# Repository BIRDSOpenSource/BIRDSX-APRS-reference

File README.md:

<div align="center">
  
</div> 

<div align="center">
  
</div>

# BIRDSX-APRS-reference
 Documentation for the APRS Reference files of the BIRDSX Satellite.

## About the BIRDSX Program:

The Mission Statement of the Project is:

> “The goal of our project is to bring diversity to the space sector and democratize the usage of space.”

The project is led by Kyushu Institute of Technology in Japan and involves students from XXX,XXX and Japan.

Satellite Names: Dragonfly (Japan), 

Stakeholders:  Our stakeholders are Kyushu Institute of Technology (Kyutech) and the Association for Radio Digital Communications (ARDC).

Project duration: 2023-2024

CubeSat: 2U (20x10x10) cm3

Weight: 1.13kg

Launch Date: 21st February 2025

BIRDS-X project is a 2U CubeSat dedicated to amateur radio communication.

## Organisation structure

```bash

├── .gitattributes
├── BIRDS_Solar-panel-attachment-procedure_v2.2.pdf
├── Manual (SML-2K1MV1) (1).pdf
├── LICENSE
└── README.md

```

## Features

## I like this project, can I help you?
You are welcome 🙂

* Give us a star ⭐
* Watch repository to be notified about updates 👀
* If you will find some errors, report them in Issues 🐞
* Try Birds designs on some real computer and let us know how it worked in Discussions. 💬
* We would greatly appreciate if you would also tell others about this ecosystem, it helps us to improve BIRDS Open Source. Thank you!

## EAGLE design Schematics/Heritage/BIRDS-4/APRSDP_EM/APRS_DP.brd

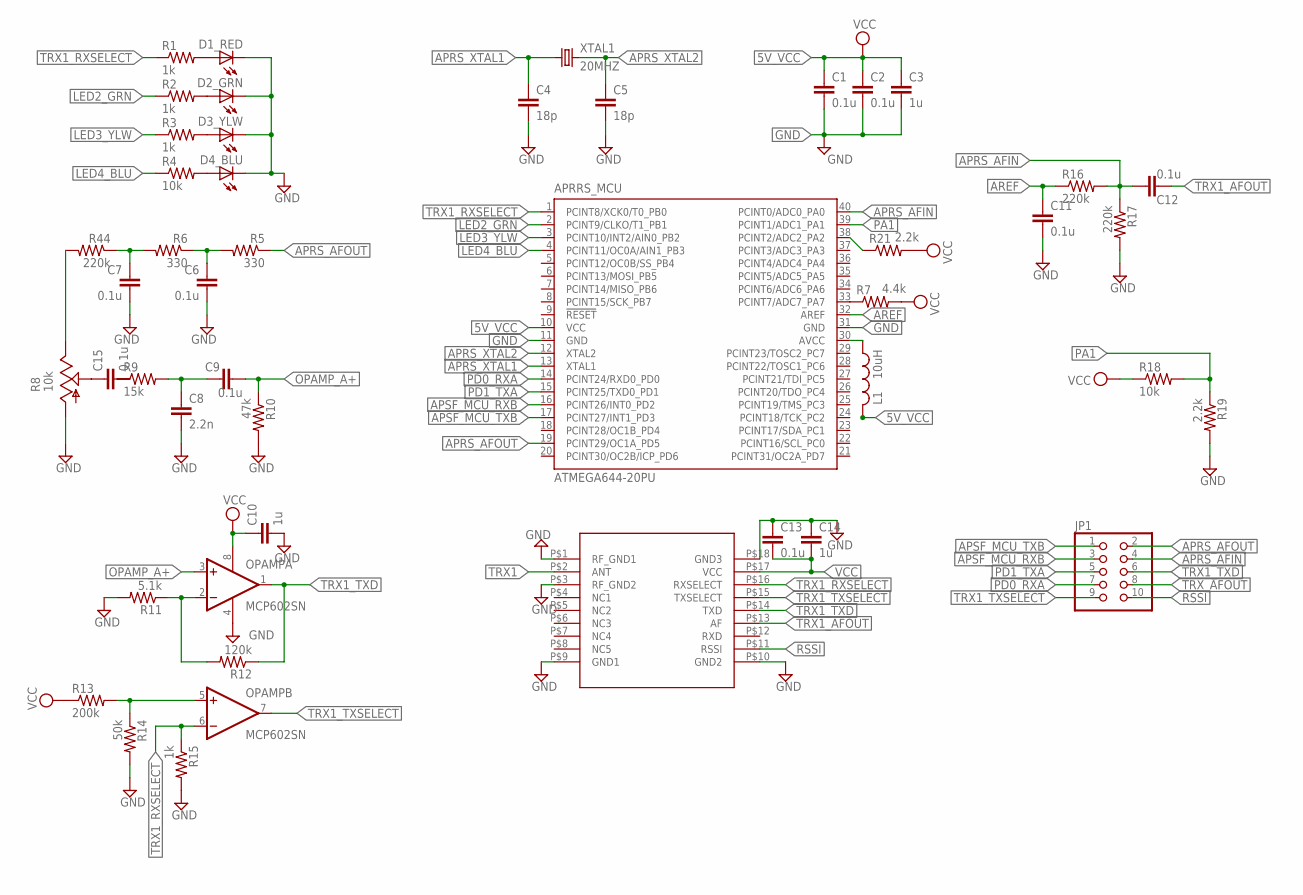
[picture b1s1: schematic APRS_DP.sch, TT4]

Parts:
APRRS_MCU: ATMEGA644-20PU; DIL40
BIM1H(TRX1)1: BIM1H
C1, C2, C6, C7, C9, C11, C12, C13, C15: 0.1u; C0805
C3, C10, C14: 1u; C0805
C4, C5: 18p; C0805
C8: 2.2n; C0805
D1_RED, D2_GRN, D3_YLW, D4_BLU: LEDSML0805; SML0805
JP1: PINHD-2X5; 2X05
L1: 10uH; L2012C
OPAMP: MCP602SN; SO08
R1, R2, R3, R15: 1k; R0805
R4, R18: 10k; R0805
R5, R6: 330; R0805
R7: 4.4k; R0805
R8: 10k; 3223W
R9: 15k; R0805
R10: 47k; R0805
R11: 5.1k; R0805
R12: 120k; R0805
R13: 200k; R0805
R14: 50k; R0805
R16, R17, R44: 220k; R0805
R19, R21: 2.2k; R0805
XTAL1: 20MHZ; SM49

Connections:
5V_VCC: APRRS_MCU.10 (VCC), C1.1, C2.1, C3.1, L1.2
APRS_AFIN: APRRS_MCU.40 (PCINT0/ADC0_PA0), C12.1, JP1.4, R16.2, R17.1
APRS_AFOUT: APRRS_MCU.19 (PCINT29/OC1A_PD5), JP1.2, R5.1
APRS_XTAL1: APRRS_MCU.13 (XTAL1), C4.1, XTAL1.1
APRS_XTAL2: APRRS_MCU.12 (XTAL2), C5.1, XTAL1.2
APSF_MCU_RXB: APRRS_MCU.16 (PCINT26/INT0_PD2), JP1.3
APSF_MCU_TXB: APRRS_MCU.17 (PCINT27/INT1_PD3), JP1.1
AREF: APRRS_MCU.32 (AREF), C11.1, R16.1
GND: APRRS_MCU.11 (GND), APRRS_MCU.31 (GND), BIM1H(TRX1)1.P$1 (RF_GND1), BIM1H(TRX1)1.P$3 (RF_GND2), BIM1H(TRX1)1.P$9 (GND1), BIM1H(TRX1)1.P$10 (GND2), BIM1H(TRX1)1.P$18 (GND3), C1.2, C2.2, C3.2, C4.2, C5.2, C6.2, C7.2, C8.2, C10.2, C11.2, C13.1, C14.1, D1_RED.C, D2_GRN.C, D3_YLW.C, D4_BLU.C, OPAMP.4 (V-), R8.1 (A), R10.2, R11.2, R14.2, R15.2, R17.2, R19.2
LED2_GRN: APRRS_MCU.2 (PCINT9/CLKO/T1_PB1), R2.1
LED3_YLW: APRRS_MCU.3 (PCINT10/INT2/AIN0_PB2), R3.1
LED4_BLU: APRRS_MCU.4 (PCINT11/OC0A/AIN1_PB3), R4.1
unnamed: APRRS_MCU.30 (AVCC), L1.1
unnamed: C6.1, R5.2, R6.1
unnamed: D1_RED.A, R1.2
unnamed: D2_GRN.A, R2.2
unnamed: D3_YLW.A, R3.2
unnamed: D4_BLU.A, R4.2
unnamed: OPAMP.2 (-IN), R11.1, R12.2
unnamed: C15.1, R8.2 (S)
unnamed: APRRS_MCU.33 (PCINT7/ADC7_PA7), R7.1
unnamed: C7.1, R6.2, R44.1
unnamed: C8.1, C9.1, R9.2
unnamed: R8.3 (E), R44.2
OPAMP_A+: C9.2, OPAMP.3 (+IN), R10.1
OPAMP_B+: OPAMP.5 (+IN), R13.2, R14.1
PA1: APRRS_MCU.39 (PCINT1/ADC1_PA1), R18.2, R19.1
PA2: APRRS_MCU.38 (PCINT2/ADC2_PA2), R21.1
PD0_RXA: APRRS_MCU.14 (PCINT24/RXD0_PD0), JP1.7
PD1_TXA: APRRS_MCU.15 (PCINT25/TXD0_PD1), JP1.5
RSSI: BIM1H(TRX1)1.P$11 (RSSI), JP1.10
TRX1: BIM1H(TRX1)1.P$2 (ANT)
TRX1_AFOUT: BIM1H(TRX1)1.P$13 (AF), C12.2
TRX1_RXSELECT: APRRS_MCU.1 (PCINT8/XCK0/T0_PB0), BIM1H(TRX1)1.P$16 (RXSELECT), OPAMP.6 (-IN), R1.1, R15.1
TRX1_TXD: BIM1H(TRX1)1.P$14 (TXD), JP1.6, OPAMP.1 (OUT), R12.1
TRX1_TXSELECT: BIM1H(TRX1)1.P$15 (TXSELECT), JP1.9, OPAMP.7 (OUT)
TRX_AFOUT: JP1.8
VCC: BIM1H(TRX1)1.P$17 (VCC), C10.1, C13.2, C14.2, OPAMP.8 (V+), R7.2, R13.1, R18.1, R21.2

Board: 4 copper layers, 46 parts (0 on the bottom side), 36 nets, no tracks yet.

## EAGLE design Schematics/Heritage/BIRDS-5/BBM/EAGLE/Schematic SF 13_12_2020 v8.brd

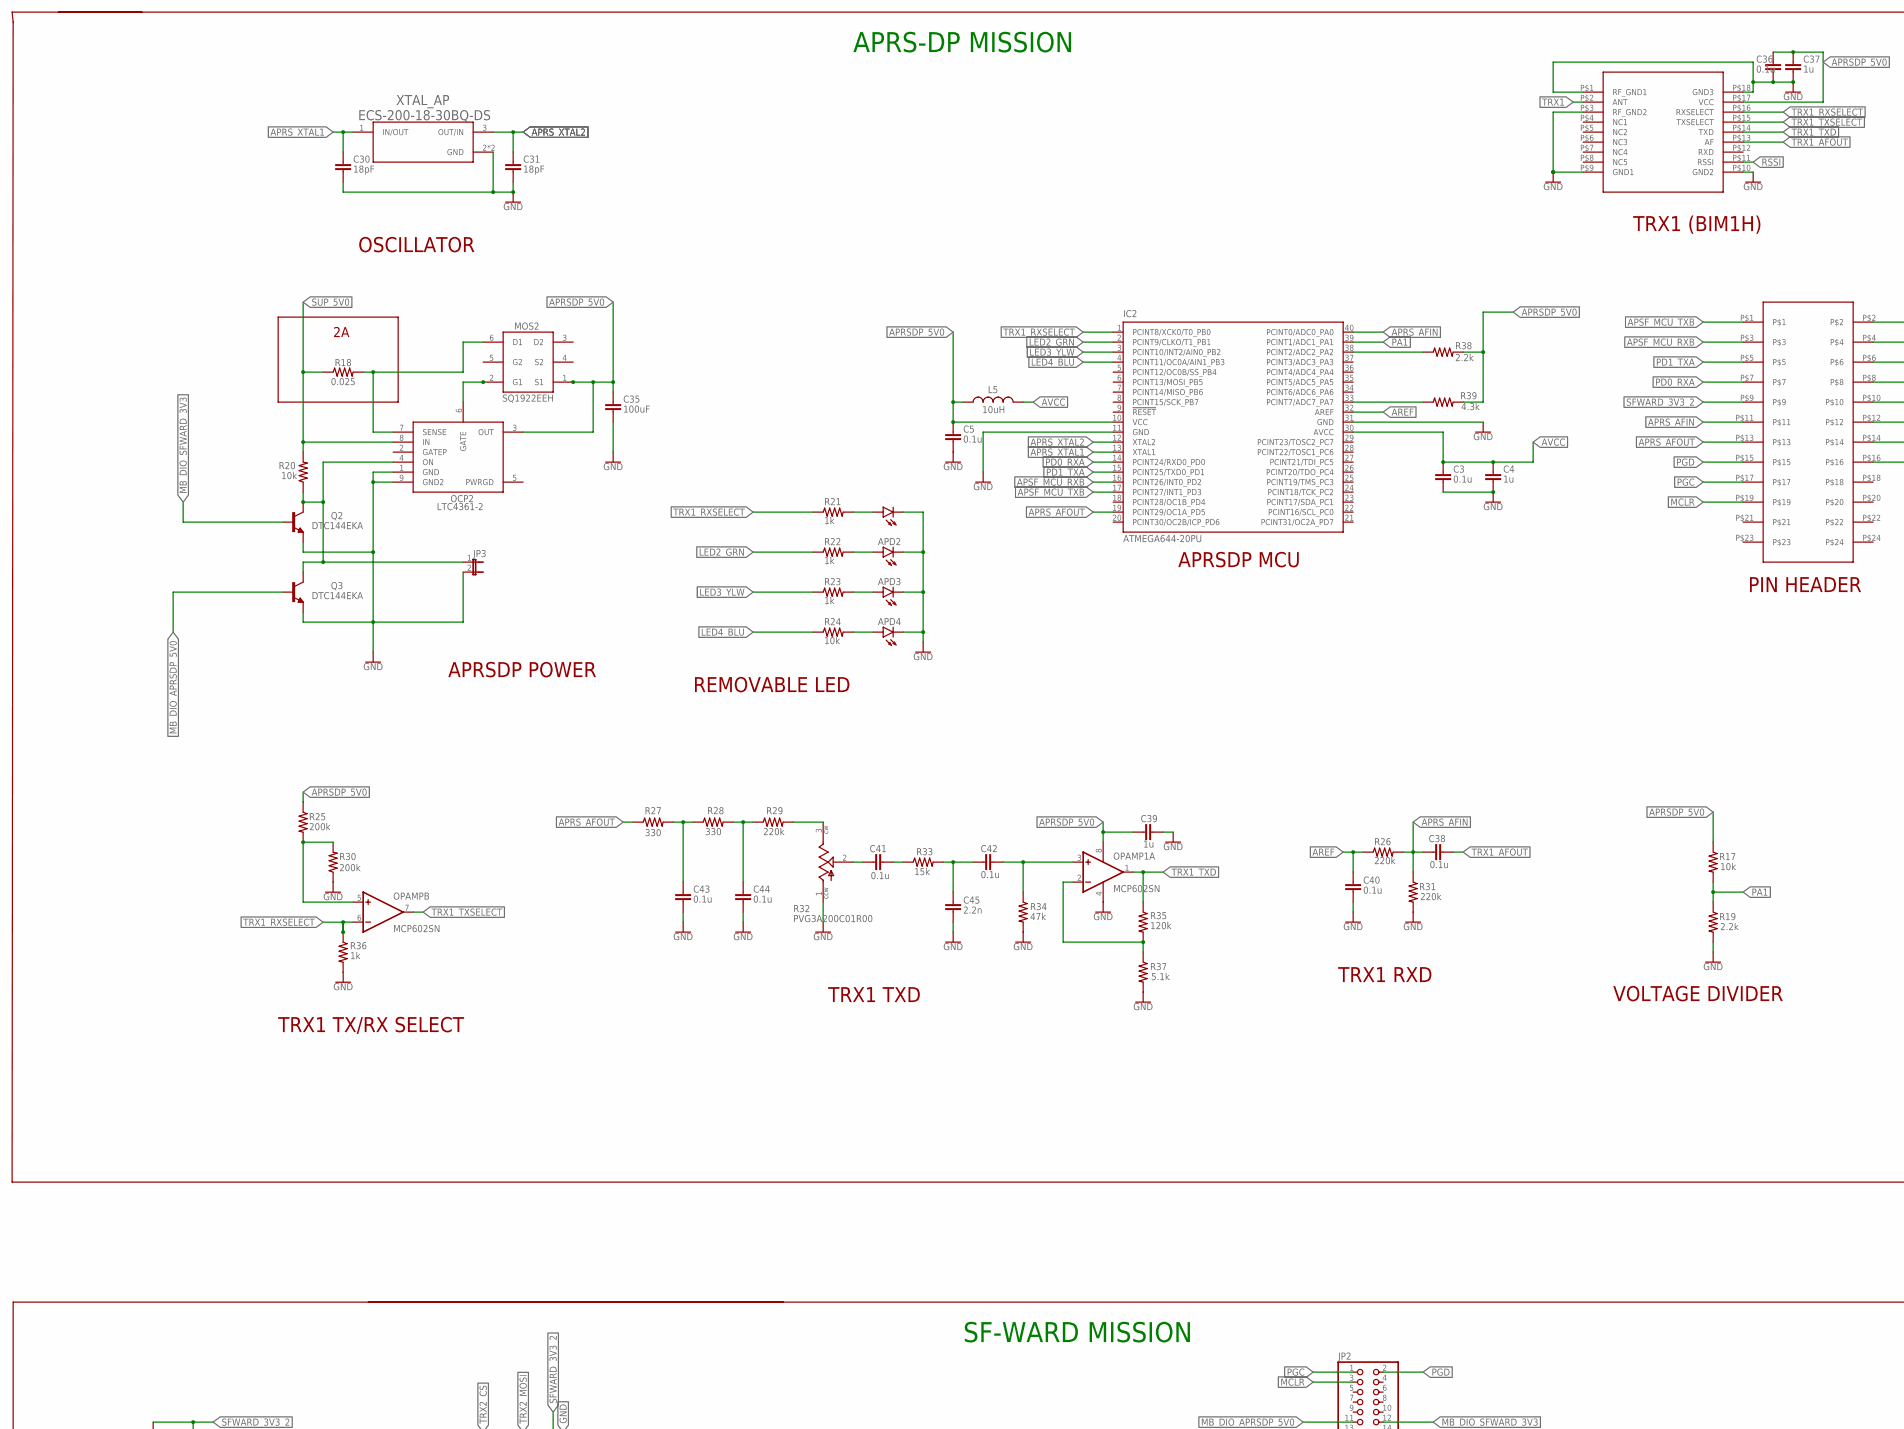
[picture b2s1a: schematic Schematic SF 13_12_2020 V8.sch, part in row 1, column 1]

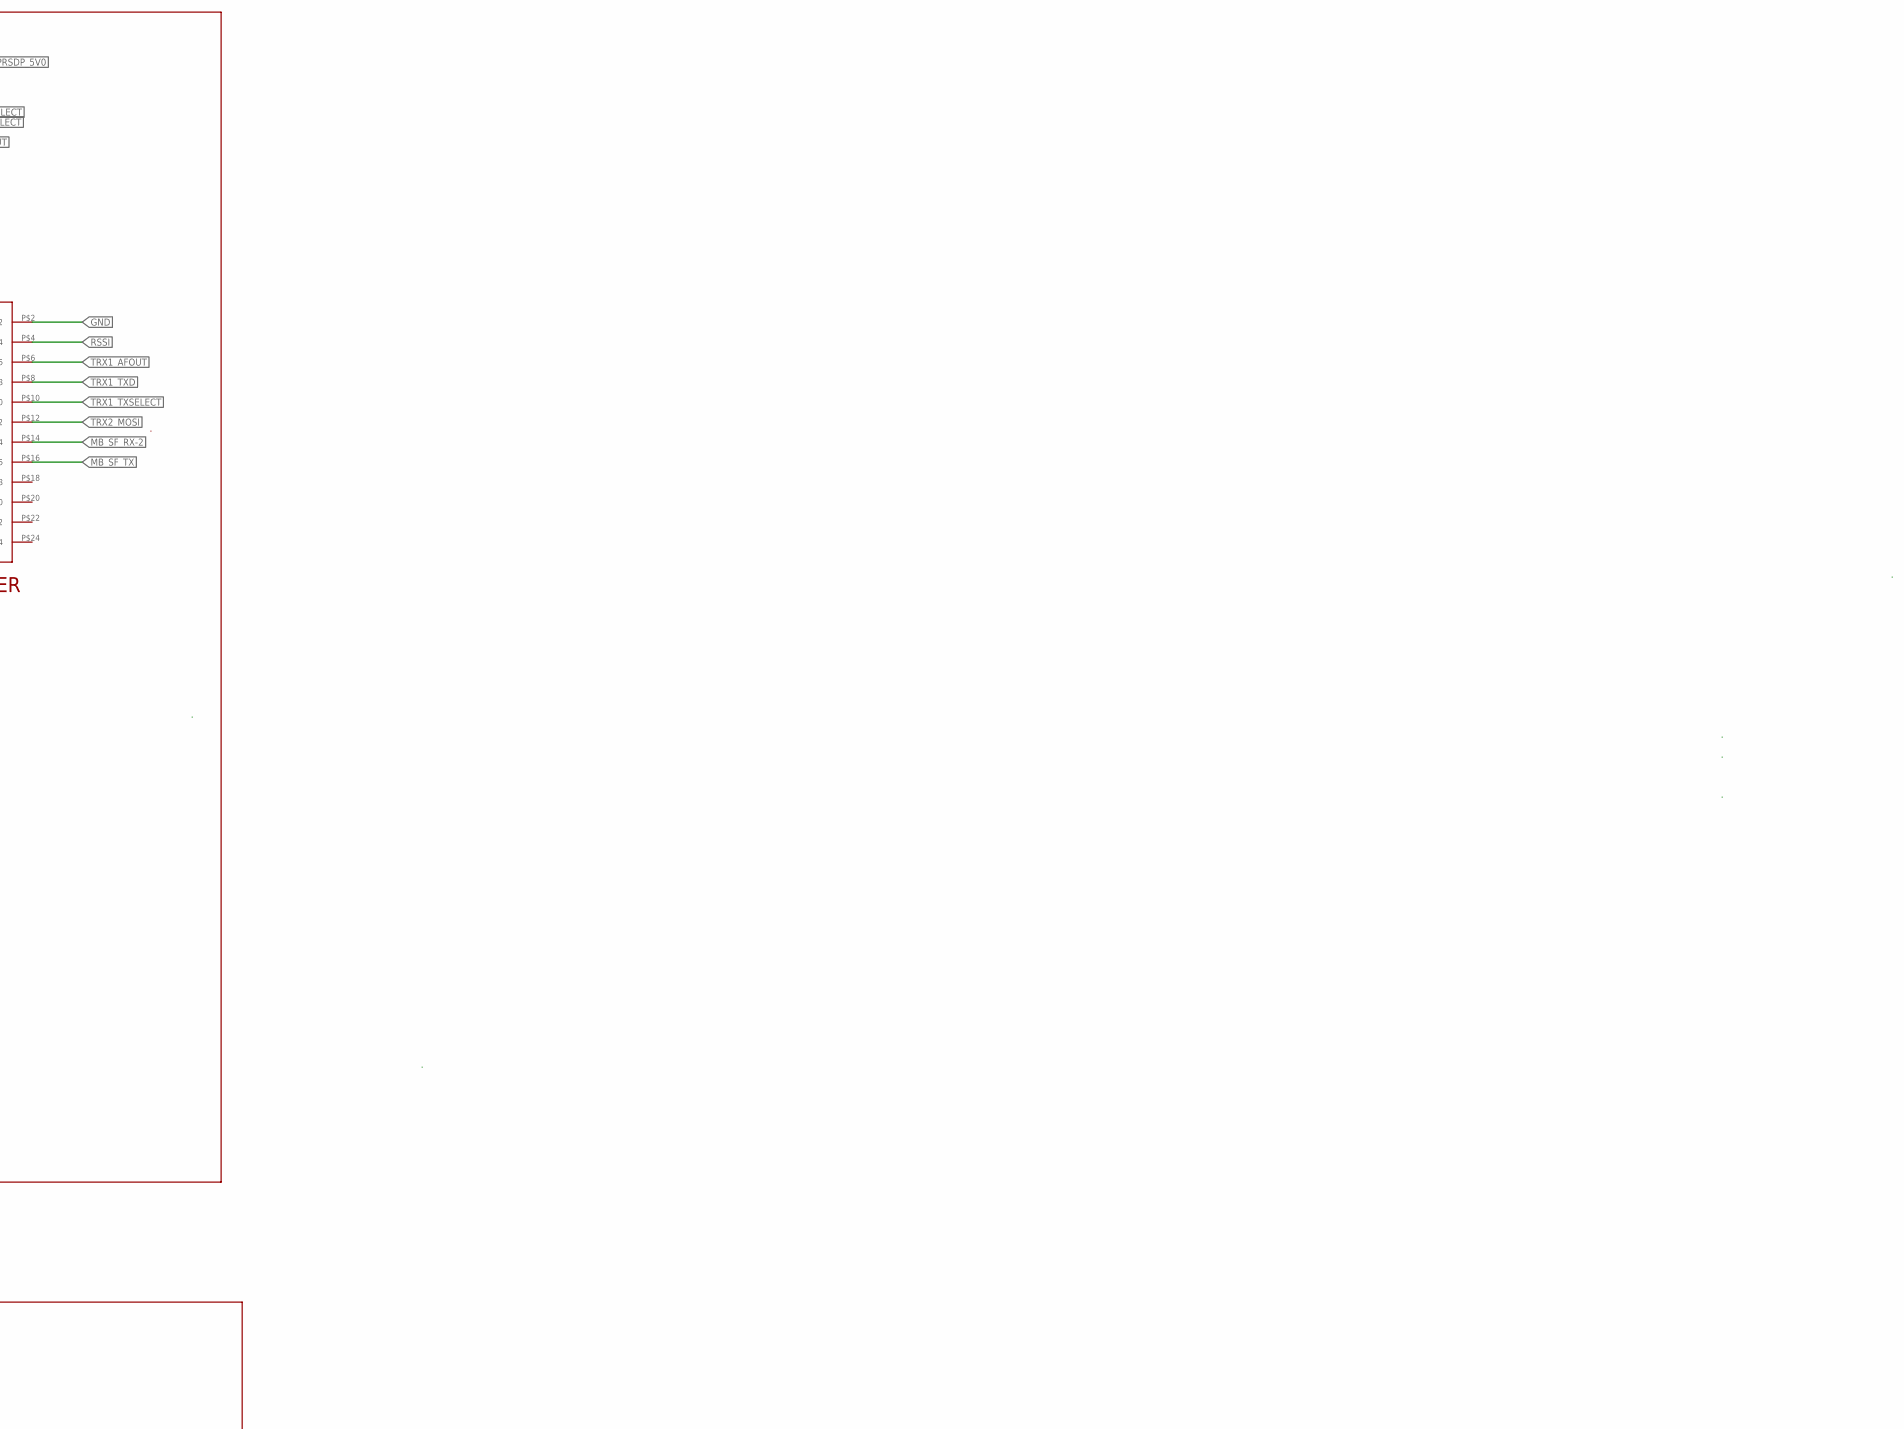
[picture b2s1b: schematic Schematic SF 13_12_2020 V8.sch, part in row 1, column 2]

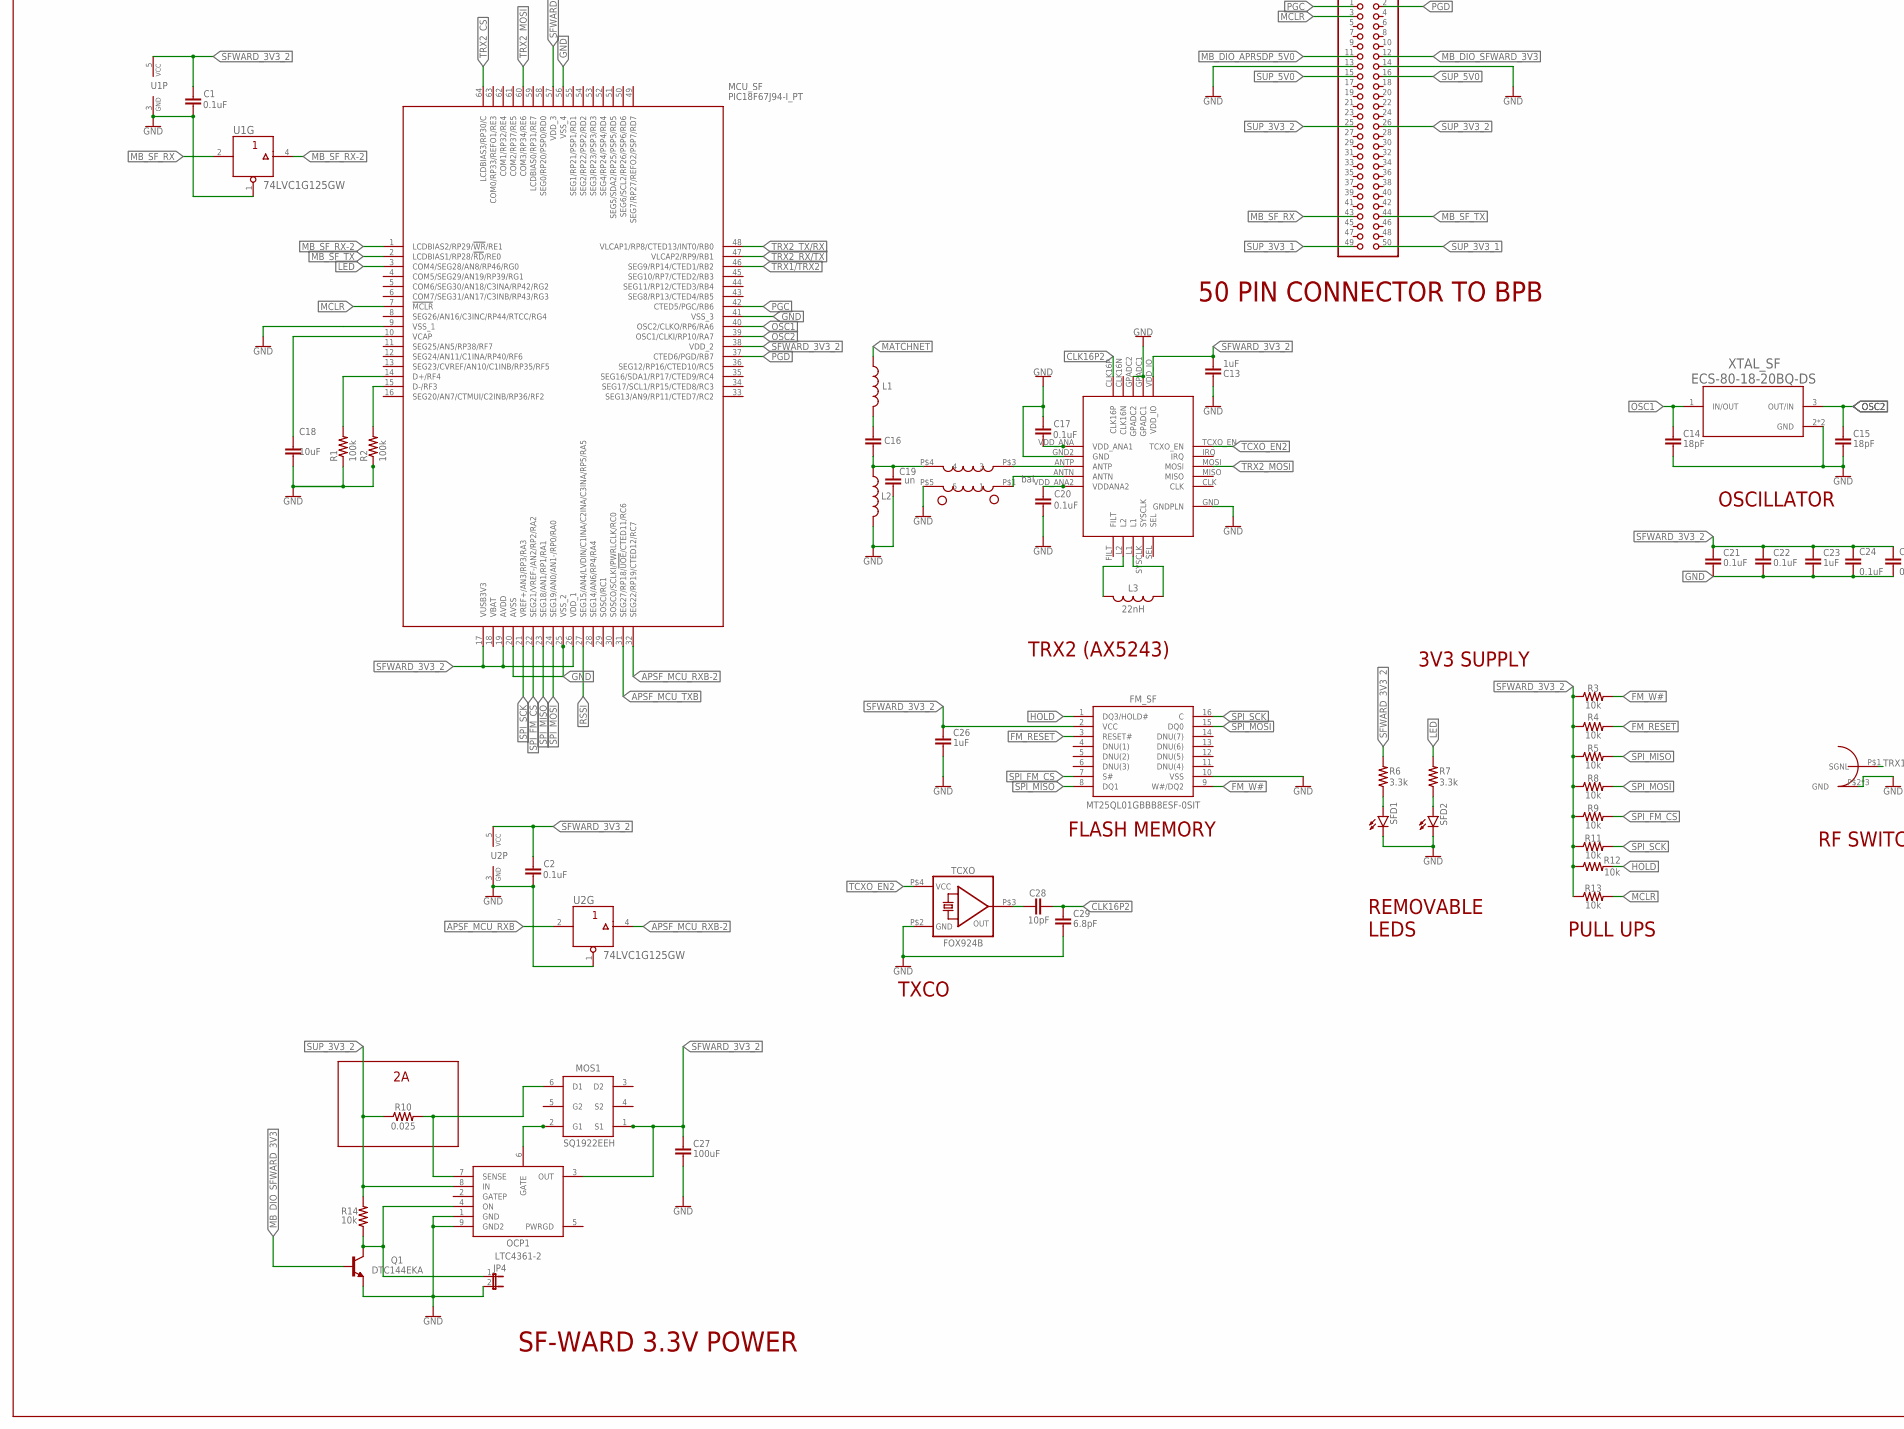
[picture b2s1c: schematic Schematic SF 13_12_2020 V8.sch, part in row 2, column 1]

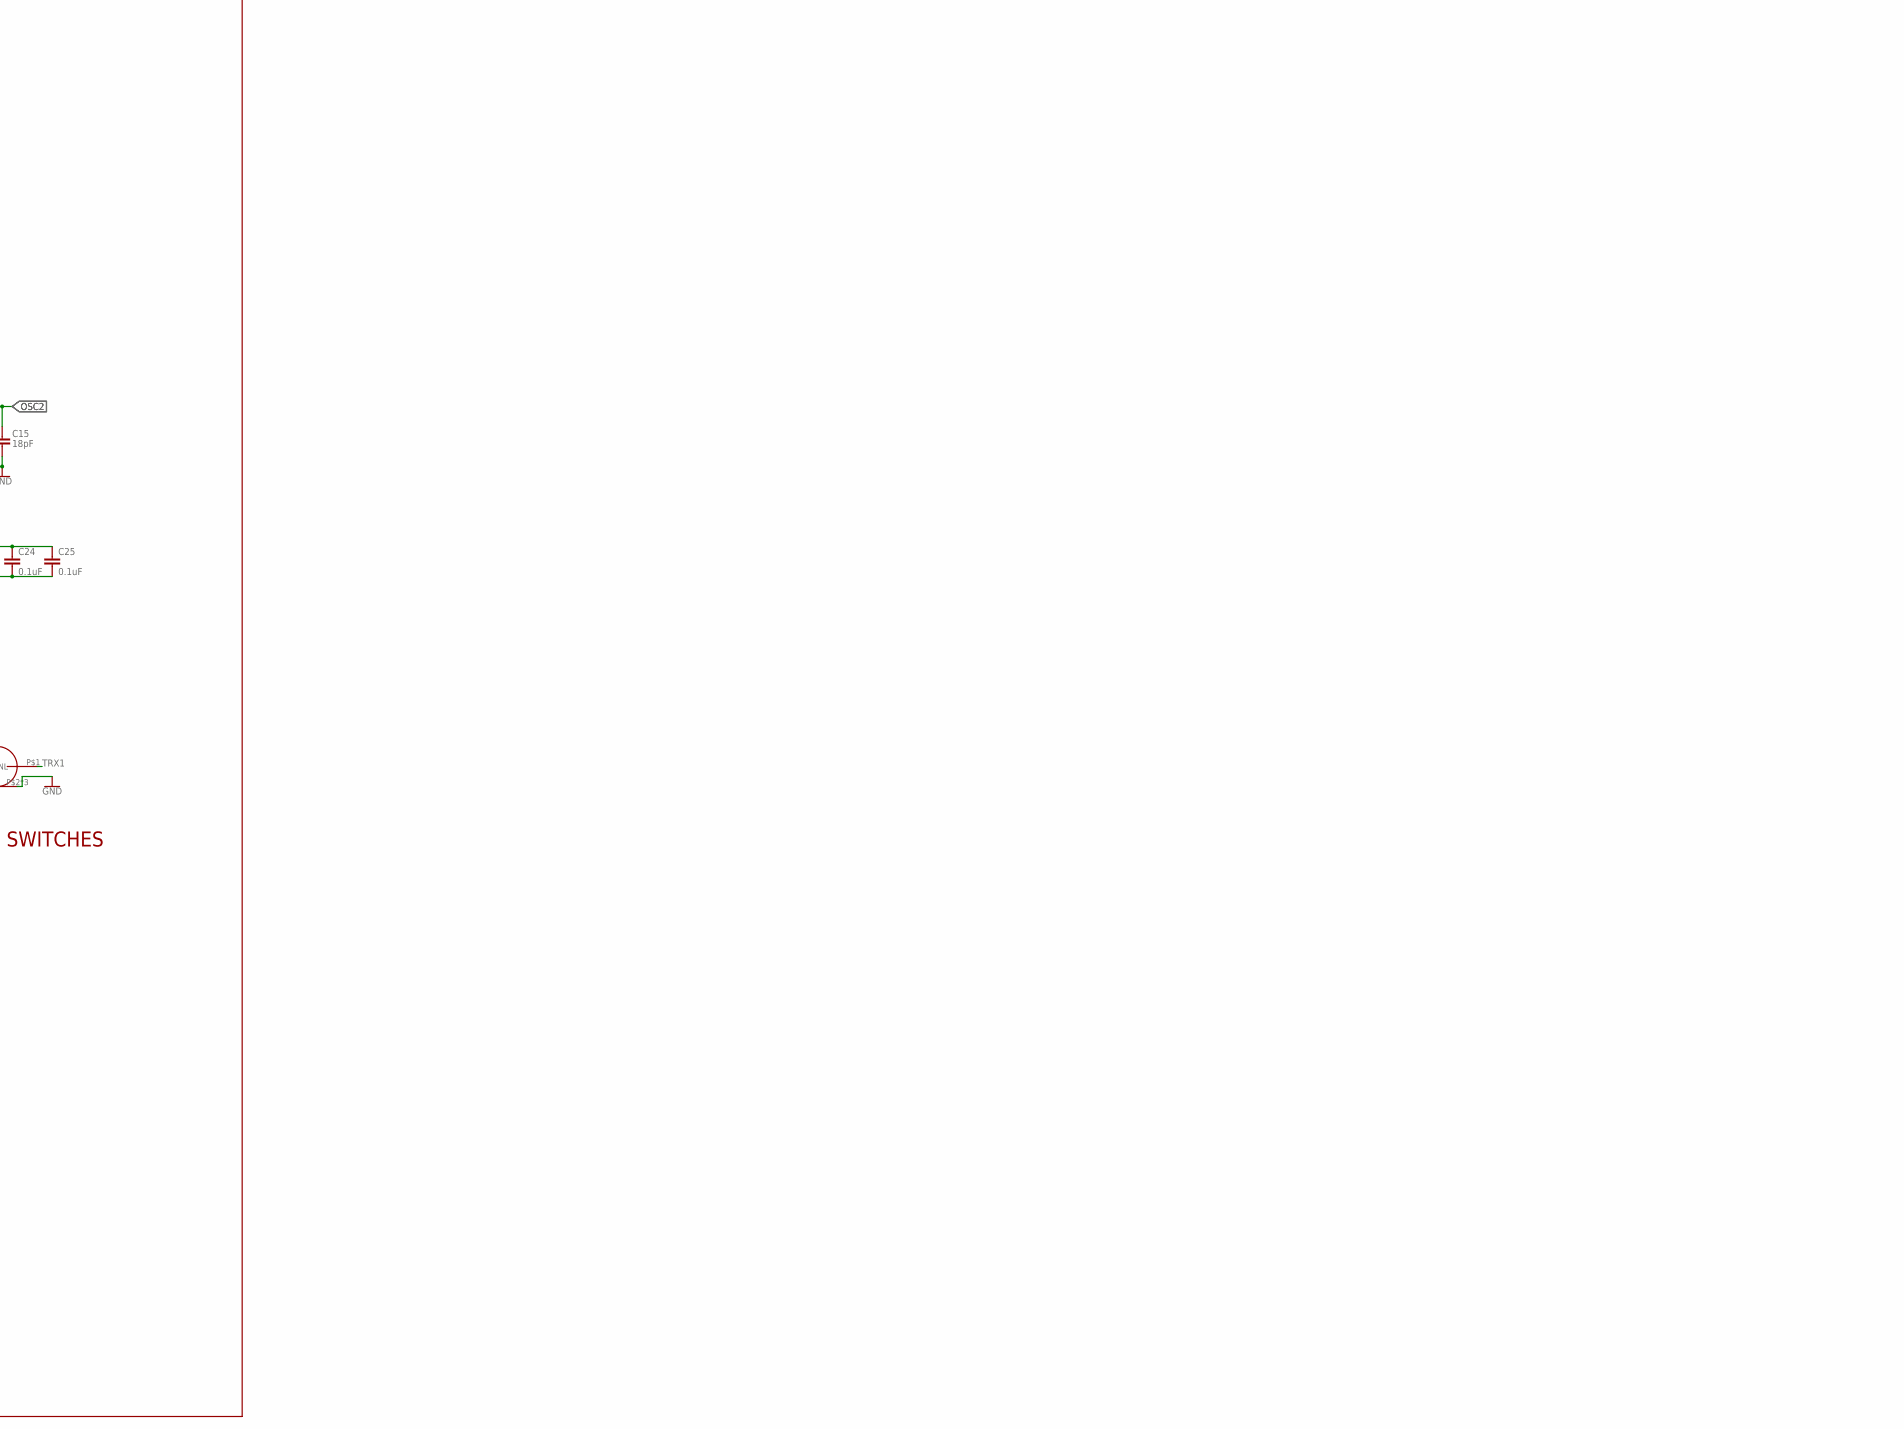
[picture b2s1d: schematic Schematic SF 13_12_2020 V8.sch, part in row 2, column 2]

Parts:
APD1, APD2, APD3, APD4: LEDSML0603; SML0603
BAL: MABA-010245-BALUN
C1, C2, C17, C20, C21, C22, C24, C25: 0.1uF; C0603
C3, C5, C36, C38, C40, C41, C42, C43, C44: 0.1u; C0603
C4, C37, C39: 1u; C0603
C13, C23, C26: 1uF; C0603
C14, C15, C30, C31: 18pF; C0603
C16, C19: C-EUC0805; C0805
C18: 10uF; C0603
C27, C35: 100uF; C0805
C28: 10pF; C0603
C29: 6.8pF; C0603
C45: 2.2n; C0603
FM_SF: MT25QL01GBBB8ESF-0SIT; SOIC127P1032X265-16N
IC2: ATMEGA644-20PU; DIL40
JP1: RAB_ACCESS
JP2: PINHD-2X25_2.00; 2X25M
JP3, JP4: JP1E; JP1
L1, L2: L-USL2012C; L2012C
L3: 22nH; L2012C
L5: 10uH; L2012C
MCU_SF: PIC18F67J94-I_PT; QFP50P1200X1200X120-64N
MOS1, MOS2: SQ1922EEH; SOT65P210X110-6N
OCP1, OCP2: LTC4361-2; DFN
OPAMP, OPAMP1: MCP602SN; SO08
Q1, Q2, Q3: DTC144EKA; SOT346-R
R1, R2: 100k; R0603
R3, R4, R5, R8, R9, R11, R12, R13, R14, R17, R20, R24: 10k; R0603
R6, R7: 3.3k; R0603
R10, R18: 0.025; R0805
R19, R38: 2.2k; R0603
R21, R22, R23, R36: 1k; R0603
R25, R30: 200k; R0603
R26, R29, R31: 220k; R0603
R27, R28: 330; R0603
R32: PVG3A200C01R00; TRIM_PVG3A200C01R00
R33: 15k; R0603
R34: 47k; R0603
R35: 120k; R0603
R37: 5.1k; R0603
R39: 4.3k; R0603
RFCON: MMCX_908_222101T
SFD1, SFD2: LEDCHIPLED_0603; CHIPLED_0603
TCXO: FOX924B
TRX1: BIM1H
TRX2: AX5243
U1, U2: 74LVC1G125GW; SOT353-1
XTAL_AP: ECS-200-18-30BQ-DS; XTAL_ECS-200-18-30BQ-DS
XTAL_SF: ECS-80-18-20BQ-DS; XTAL_ECS-80-18-20BQ-DS

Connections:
APRSDP_5V0: C5.2, C35.1, C36.1, C37.1, C39.1, IC2.10 (VCC), L5.1, MOS2.1 (S1), OCP2.3 (OUT), OPAMP1.8 (V+), R17.1, R25.1, R38.2, R39.2, TRX1.P$17 (VCC)
APRS_AFIN: C38.1, IC2.40 (PCINT0/ADC0_PA0), JP1.P$11, R26.2, R31.1
APRS_AFOUT: IC2.19 (PCINT29/OC1A_PD5), JP1.P$13, R27.1
APRS_XTAL1: C30.1, IC2.13 (XTAL1), XTAL_AP.1 (IN/OUT)
APRS_XTAL2: C31.1, IC2.12 (XTAL2), XTAL_AP.3 (OUT/IN)
APSF_MCU_RXB: IC2.16 (PCINT26/INT0_PD2), JP1.P$3, U2.2 (A)
APSF_MCU_RXB-2: MCU_SF.32 (SEG22/RP19/CTED12/RC7), U2.4 (Y)
APSF_MCU_TXB: IC2.17 (PCINT27/INT1_PD3), JP1.P$1, MCU_SF.31 (SEG27/RP18/!UOE!/CTED11/RC6)
AREF: C40.1, IC2.32 (AREF), R26.1
AVCC: C3.1, C4.1, IC2.30 (AVCC), L5.2
CLK16P2: C28.2, C29.1, TRX2.CLK16P
FM_RESET: FM_SF.3 (RESET#), R4.2
FM_W#: FM_SF.9 (W#/DQ2), R3.2
GATE3: MOS1.2 (G1), OCP1.6 (GATE)
GATE4: MOS2.2 (G1), OCP2.6 (GATE)
GND: APD1.C, APD2.C, APD3.C, APD4.C, BAL.P$5 (5), C1.1, C2.1, C3.2, C4.2, C5.1, C13.1, C14.2, C15.2, C17.2, C18.2, C19.2, C20.2, C21.2, C22.2, C23.2, C24.2, C25.2, C26.2, C27.2, C29.2, C30.2, C31.2, C35.2, C36.2, C37.2, C39.2, C40.2, C43.2, C44.2, C45.2, FM_SF.10 (VSS), IC2.11 (GND), IC2.31 (GND), JP1.P$2, JP2.13, JP2.14, JP3.2, JP4.2, L2.2, MCU_SF.9 (VSS_1), MCU_SF.20 (AVSS), MCU_SF.25 (VSS_2), MCU_SF.41 (VSS_3), MCU_SF.56 (VSS_4), OCP1.1 (GND), OCP1.9 (GND2), OCP2.1 (GND), OCP2.9 (GND2), OPAMP1.4 (V-), Q1.1 (E), Q2.1 (E), Q3.1 (E), R1.1, R2.1, R19.2, R30.1, R31.2, R32.1 (CCW), R34.2, R36.2, R37.2, RFCON.P$2 (GND), RFCON.P$3 (GND), RFCON.P$4 (GND), SFD1.C, SFD2.C, TCXO.P$2 (GND), TRX1.P$1 (RF_GND1), TRX1.P$3 (RF_GND2), TRX1.P$9 (GND1), TRX1.P$10 (GND2), TRX1.P$18 (GND3), TRX2.GND (GNDPLN), TRX2.GND2 (GND), TRX2.GPADC1, TRX2.GPADC2, U1.1 (OEN), U1.3 (GND), U2.1 (OEN), U2.3 (GND), XTAL_AP.2 (GND), XTAL_AP.4 (GND), XTAL_SF.2 (GND), XTAL_SF.4 (GND)
HOLD: FM_SF.1 (DQ3/HOLD#), R12.2
LED: MCU_SF.3 (COM4/SEG28/AN8/RP46/RG0), R7.2
LED2_GRN: IC2.2 (PCINT9/CLKO/T1_PB1), R22.1
LED3_YLW: IC2.3 (PCINT10/INT2/AIN0_PB2), R23.1
LED4_BLU: IC2.4 (PCINT11/OC0A/AIN1_PB3), R24.1
MATCHNET: L1.1
MB_DIO_APRSDP_5V0: JP2.11, Q3.2 (B)
MB_DIO_SFWARD_3V3: JP2.12, Q1.2 (B), Q2.2 (B)
MB_SF_RX: JP2.43, U1.2 (A)
MB_SF_RX-2: JP1.P$14, MCU_SF.1 (LCDBIAS2/RP29/!WR!/RE1), U1.4 (Y)
MB_SF_TX: JP1.P$16, JP2.44, MCU_SF.2 (LCDBIAS1/RP28/!RD!/RE0)
MCLR: JP1.P$19, JP2.3, MCU_SF.7 (!MCLR), R13.2
unnamed: C18.1, MCU_SF.10 (VCAP)
unnamed: MCU_SF.14 (D+/RF4), R1.2
unnamed: MCU_SF.15 (D-/RF3), R2.2
unnamed: R6.1, SFD1.A
unnamed: R29.2, R32.3 (CW)
unnamed: R7.1, SFD2.A
unnamed: APD1.A, R21.2
unnamed: APD2.A, R22.2
unnamed: APD3.A, R23.2
unnamed: APD4.A, R24.2
unnamed: C43.1, R27.2, R28.1
unnamed: C44.1, R28.2, R29.1
unnamed: C42.1, C45.1, R33.2
unnamed: C41.2, R33.1
unnamed: OPAMP1.2 (-IN), R35.2, R37.1
unnamed: OPAMP.5 (+IN), R25.2, R30.2
unnamed: C41.1, R32.2 (WIPER)
unnamed: IC2.38 (PCINT2/ADC2_PA2), R38.1
unnamed: C20.1, TRX2.VDD_ANA2 (VDDANA2)
unnamed: C17.1, TRX2.VDD_ANA (VDD_ANA1)
unnamed: L3.2, TRX2.L2
unnamed: IC2.33 (PCINT7/ADC7_PA7), R39.1
unnamed: L3.1, TRX2.L1
unnamed: C16.1, L1.2
unnamed: BAL.P$4 (4), C16.2, C19.1, L2.1
unnamed: BAL.P$1 (1), TRX2.ANTN
unnamed: BAL.P$3 (3), TRX2.ANTP
unnamed: C28.1, TCXO.P$3 (OUT)
ON3: JP4.1, OCP1.4 (ON), Q1.3 (C), R14.1
ON4: JP3.1, OCP2.4 (ON), Q2.3 (C), Q3.3 (C), R20.1
OPAMP_A+: C42.2, OPAMP1.3 (+IN), R34.1
OSC1: C14.1, MCU_SF.40 (OSC2/CLKO/RP6/RA6), XTAL_SF.1 (IN/OUT)
OSC2: C15.1, MCU_SF.39 (OSC1/CLKI/RP10/RA7), XTAL_SF.3 (OUT/IN)
PA1: IC2.39 (PCINT1/ADC1_PA1), R17.2, R19.1
PD0_RXA: IC2.14 (PCINT24/RXD0_PD0), JP1.P$7
PD1_TXA: IC2.15 (PCINT25/TXD0_PD1), JP1.P$5
PGC: JP1.P$17, JP2.1, MCU_SF.42 (CTED5/PGC/RB6)
PGD: JP1.P$15, JP2.2, MCU_SF.37 (CTED6/PGD/RB7)
RSSI: JP1.P$4, MCU_SF.27 (SEG15/AN4/LVDIN/C1INA/C2INA/C3INA/RP5/R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), TRX1.P$11 (RSSI)
SENSE3: MOS1.6 (D1), OCP1.7 (SENSE), R10.2
SENSE4: MOS2.6 (D1), OCP2.7 (SENSE), R18.2
SFWARD_3V3_2: C1.2, C2.2, C13.2, C21.1, C22.1, C23.1, C24.1, C25.1, C26.1, C27.1, FM_SF.2 (VCC), JP1.P$9, MCU_SF.17 (VUSB3V3), MCU_SF.19 (AVDD), MCU_SF.26 (VDD_1), MCU_SF.38 (VDD_2), MCU_SF.57 (VDD_3), MOS1.1 (S1), OCP1.3 (OUT), R3.1, R4.1, R5.1, R6.2, R8.1, R9.1, R11.1, R12.1, R13.1, TRX2.VDD_IO, U1.5 (VCC), U2.5 (VCC)
SPI_FM_CS: FM_SF.7 (S#), MCU_SF.22 (SEG21/VREF-/AN2/RP2/RA2), R9.2
SPI_MISO: FM_SF.8 (DQ1), MCU_SF.23 (SEG18/AN1/RP1/RA1), R5.2
SPI_MOSI: FM_SF.15 (DQ0), MCU_SF.24 (SEG19/AN0/AN1-/RP0/RA0), R8.2
SPI_SCK: FM_SF.16 (C), MCU_SF.21 (VREF+/AN3/RP3/RA3), R11.2
SUP_3V3_1: JP2.49, JP2.50
SUP_3V3_2: JP2.25, JP2.26, OCP1.8 (IN), R10.1, R14.2
SUP_5V0: JP2.15, JP2.16, OCP2.8 (IN), R18.1, R20.2
TCXO_EN2: TCXO.P$4 (VCC), TRX2.TCXO_EN
TRX1: RFCON.P$1 (SGNL), TRX1.P$2 (ANT)
TRX1/TRX2: MCU_SF.46 (SEG9/RP14/CTED1/RB2)
TRX1_AFOUT: C38.2, JP1.P$6, TRX1.P$13 (AF)
TRX1_RXSELECT: IC2.1 (PCINT8/XCK0/T0_PB0), OPAMP.6 (-IN), R21.1, R36.1, TRX1.P$16 (RXSELECT)
TRX1_TXD: JP1.P$8, OPAMP1.1 (OUT), R35.1, TRX1.P$14 (TXD)
TRX1_TXSELECT: JP1.P$10, OPAMP.7 (OUT), TRX1.P$15 (TXSELECT)
TRX2_CS: MCU_SF.64 (LCDBIAS3/RP30/C)
TRX2_MOSI: JP1.P$12, MCU_SF.60 (COM3/RP34/RE6), TRX2.MOSI
TRX2_RX/TX: MCU_SF.47 (VLCAP2/RP9/RB1)
TRX2_TX/RX: MCU_SF.48 (VLCAP1/RP8/CTED13/INT0/RB0)
V+: OPAMP.8 (V+)
V-: OPAMP.4 (V-)

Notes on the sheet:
OSCILLATOR
APRSDP POWER
TRX1 TX/RX SELECT
PIN HEADER
TRX1 TXD
TRX1 RXD
TRX1 (BIM1H)
VOLTAGE DIVIDER
REMOVABLE LED
TRX2 (AX5243)
TXCO
RF SWITCHES
FLASH MEMORY
SF-WARD 3.3V POWER
PULL UPS
REMOVABLE LEDS
3V3 SUPPLY
SF-WARD MISSION
APRS-DP MISSION
50 PIN CONNECTOR TO BPB
APRSDP MCU

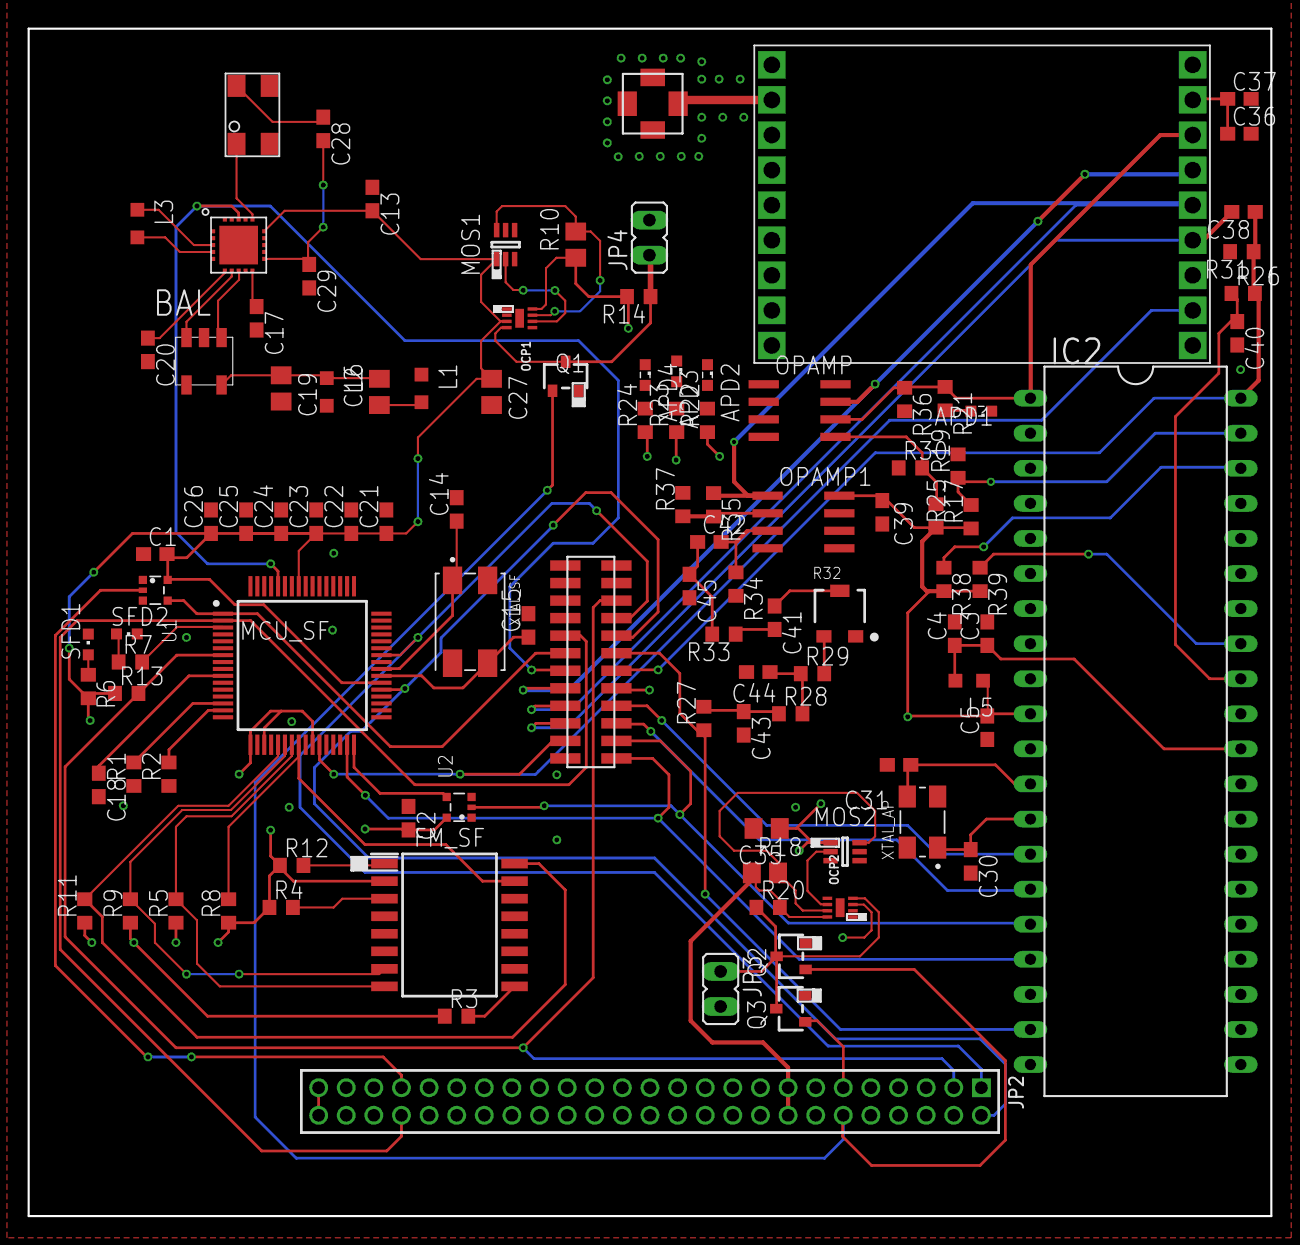
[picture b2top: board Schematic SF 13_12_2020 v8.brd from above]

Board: 4 copper layers, 90.0 x 86.0 mm, 107 parts (0 on the bottom side), 83 nets.

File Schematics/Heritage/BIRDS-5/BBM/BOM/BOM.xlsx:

Column1
Partlist exported from C:/Users/MUJUNI/Desktop/Shematics V2/Schematic SF 1_12_2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
APD1 LEDSML0603 SML0603 LED
APD2 LEDSML0603 SML0603 LED
APD3 LEDSML0603 SML0603 LED
APD4 LEDSML0603 SML0603 LED
BAL MABA-010245-BALUN MABA-010245-BALUN MABA-010245-BALUN
C1 0.1uF CC0603 C0603 CAPACITOR, European symbol NONE C
C2 0.1uF CC0603 C0603 CAPACITOR, European symbol NONE C
C3 0.1u CC0603 C0603 CAPACITOR, European symbol NONE C
C4 1u CC0603 C0603 CAPACITOR, European symbol NONE C
C5 0.1u CC0603 C0603 CAPACITOR, European symbol NONE C
C13 1uF CC0603 C0603 CAPACITOR, European symbol NONE C
C14 18pF CC0603 C0603 CAPACITOR, European symbol NONE C
C15 18pF CC0603 C0603 CAPACITOR, European symbol NONE C
C16 C-EUC0805 C0805 CAPACITOR, European symbol C
C17 0.1uF CC0603 C0603 CAPACITOR, European symbol NONE C
C18 10uF C-EUC0603 C0603 CAPACITOR, European symbol C
C19 C-EUC0805 C0805 CAPACITOR, European symbol C
C20 0.1uF CC0603 C0603 CAPACITOR, European symbol NONE C
C21 0.1uF C-EUC0603 C0603 CAPACITOR, European symbol C
C22 0.1uF C-EUC0603 C0603 CAPACITOR, European symbol C
C23 1uF C-EUC0603 C0603 CAPACITOR, European symbol C
C24 0.1uF C-EUC0603 C0603 CAPACITOR, European symbol C
C25 0.1uF C-EUC0603 C0603 CAPACITOR, European symbol C
C26 1uF C-EUC0603 C0603 CAPACITOR, European symbol C
C27 100uF C0805(2012) C0805
C28 10pF CC0603 C0603 CAPACITOR, European symbol NONE C
C29 6.8pF CC0603 C0603 CAPACITOR, European symbol NONE C
C30 18pF CC0603 C0603 CAPACITOR, European symbol NONE C
C31 18pF CC0603 C0603 CAPACITOR, European symbol NONE C
C35 100uF C0805(2012) C0805
C36 0.1u CC0603 C0603 CAPACITOR, European symbol NONE C
C37 1u CC0603 C0603 CAPACITOR, European symbol NONE C
C38 0.1u CC0603 C0603 CAPACITOR, European symbol NONE C
C39 1u CC0603 C0603 CAPACITOR, European symbol NONE C
C40 0.1u CC0603 C0603 CAPACITOR, European symbol NONE C
C41 0.1u CC0603 C0603 CAPACITOR, European symbol NONE C
C42 0.1u CC0603 C0603 CAPACITOR, European symbol NONE C
C43 0.1u CC0603 C0603 CAPACITOR, European symbol NONE C
C44 0.1u CC0603 C0603 CAPACITOR, European symbol NONE C
C45 2.2n CC0603 C0603 CAPACITOR, European symbol NONE C
FM_SF MT25QL01GBBB8ESF-0SIT MT25QL01GBBB8ESF-0SIT SOIC127P1032X265-16N IC FLASH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
IC2 ATMEGA644-20PU ATMEGA644-20PU DIL40 8-bit Microcontroller with 64K Bytes In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
JP1 RAB_ACCESS RAB_ACCESS RAB_ACCESS
JP2 PINHD-2X25_2.00 2X25M PIN HEADER
JP3 JP1E JP1 JUMPER 61
JP4 JP1E JP1 JUMPER 61
L1 L-USL2012C L2012C INDUCTOR, American symbol L
L2 L-USL2012C L2012C INDUCTOR, American symbol L
L3 22nH L-USL2012C L2012C INDUCTOR, American symbol L
L5 10uH L-USL2012C L2012C INDUCTOR, American symbol L
MCU_SF PIC18F67J94-I_PT PIC18F67J94-I_PT QFP50P1200X1200X120-64N MCU 8-Bit 128K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
MOS1 SQ1922EEH SQ1922EEH SOT65P210X110-6N
MOS2 SQ1922EEH SQ1922EEH SOT65P210X110-6N
OCP1 LTC4361-2 LTC4361-2 DFN
OCP2 LTC4361-2 LTC4361-2 DFN
OPAMP MCP602SN MCP602SN SO08 Single Op Amp 2.7V to 6.0V Single Supply CMOS
OPAMP1 MCP602SN MCP602SN SO08 Single Op Amp 2.7V to 6.0V Single Supply CMOS
Q1 DTC144EKA DTC144EKA SOT346-R
Q2 DTC144EKA DTC144EKA SOT346-R
Q3 DTC144EKA DTC144EKA SOT346-R
R1 100k R-US_R0603 R0603 RESISTOR, American symbol R
R2 100k R-US_R0603 R0603 RESISTOR, American symbol R
R3 10k R-US_R0603 R0603 RESISTOR, American symbol R
R4 10k R-US_R0603 R0603 RESISTOR, American symbol R
R5 10k R-US_R0603 R0603 RESISTOR, American symbol R
R6 3.3k R-US_R0603 R0603 RESISTOR, American symbol R
R7 3.3k R-US_R0603 R0603 RESISTOR, American symbol R
R8 10k R-US_R0603 R0603 RESISTOR, American symbol R
R9 10k R-US_R0603 R0603 RESISTOR, American symbol R
R10 0.025 R0805(2012) R0805
R11 10k R-US_R0603 R0603 RESISTOR, American symbol R
R12 10k R-US_R0603 R0603 RESISTOR, American symbol R
R13 10k R-US_R0603 R0603 RESISTOR, American symbol R
R14 10k R-US_R0603 R0603 RESISTOR, American symbol R
R17 10k R-US_R0603 R0603 RESISTOR, American symbol R
R18 0.025 R-US_R0805 R0805 RESISTOR, American symbol R
R19 2.2k R-US_R0603 R0603 RESISTOR, American symbol R
R20 10k R-US_R0603 R0603 RESISTOR, American symbol R
R21 1k R-US_R0603 R0603 RESISTOR, American symbol R
R22 1k R-US_R0603 R0603 RESISTOR, American symbol R
R23 1k R-US_R0603 R0603 RESISTOR, American symbol R
R24 10k R-US_R0603 R0603 RESISTOR, American symbol R
R25 200k R-US_R0603 R0603 RESISTOR, American symbol R
R26 220k R-US_R0603 R0603 RESISTOR, American symbol R
R27 330 R-US_R0603 R0603 RESISTOR, American symbol R
R28 330 R-US_R0603 R0603 RESISTOR, American symbol R
R29 220k R-US_R0603 R0603 RESISTOR, American symbol R
R30 200k R-US_R0603 R0603 RESISTOR, American symbol R
R31 220k R-US_R0603 R0603 RESISTOR, American symbol R
R32 PVG3A200C01R00 PVG3A200C01R00 TRIM_PVG3A200C01R00 Res Cermet Trimmer 20 Ohm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
R33 15k R-US_R0603 R0603 RESISTOR, American symbol R
R34 47k R-US_R0603 R0603 RESISTOR, American symbol R
R35 120k R-US_R0603 R0603 RESISTOR, American symbol R
R36 1k R-US_R0603 R0603 RESISTOR, American symbol R
R37 5.1k R-US_R0603 R0603 RESISTOR, American symbol R
R38 2.2k R-US_R0603 R0603 RESISTOR, American symbol R
R39 4.3k R-US_R0603 R0603 RESISTOR, American symbol R
RFCON MMCX_908_222101T MMCX_908_222101T MMCX_908_222101T
SFD1 LEDCHIPLED_0603 CHIPLED_0603 LED
SFD2 LEDCHIPLED_0603 CHIPLED_0603 LED
TCXO FOX924B FOX924B FOX924B
TRX1 BIM1H BIM1H BIM1H
TRX2 AX5243 AX5243 AX5243
U1 74LVC1G125GW 74LVC1G125GW SOT353-1 Bus buffer/line driver; 3-state
U2 74LVC1G125GW 74LVC1G125GW SOT353-1 Bus buffer/line driver; 3-state
XTAL_AP ECS-200-18-30BQ-DS ECS-200-18-30BQ-DS XTAL_ECS-200-18-30BQ-DS The ECX-5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
XTAL_SF ECS-80-18-20BQ-DS ECS-80-18-20BQ-DS XTAL_ECS-80-18-20BQ-DS compact SMD 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

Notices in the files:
parts and their libraries:
SparkFun-PowerSymbols: Licensing: Creative Commons ShareAlike 4.0 International - https://creativecommons.org/licenses/by-sa/4.0
